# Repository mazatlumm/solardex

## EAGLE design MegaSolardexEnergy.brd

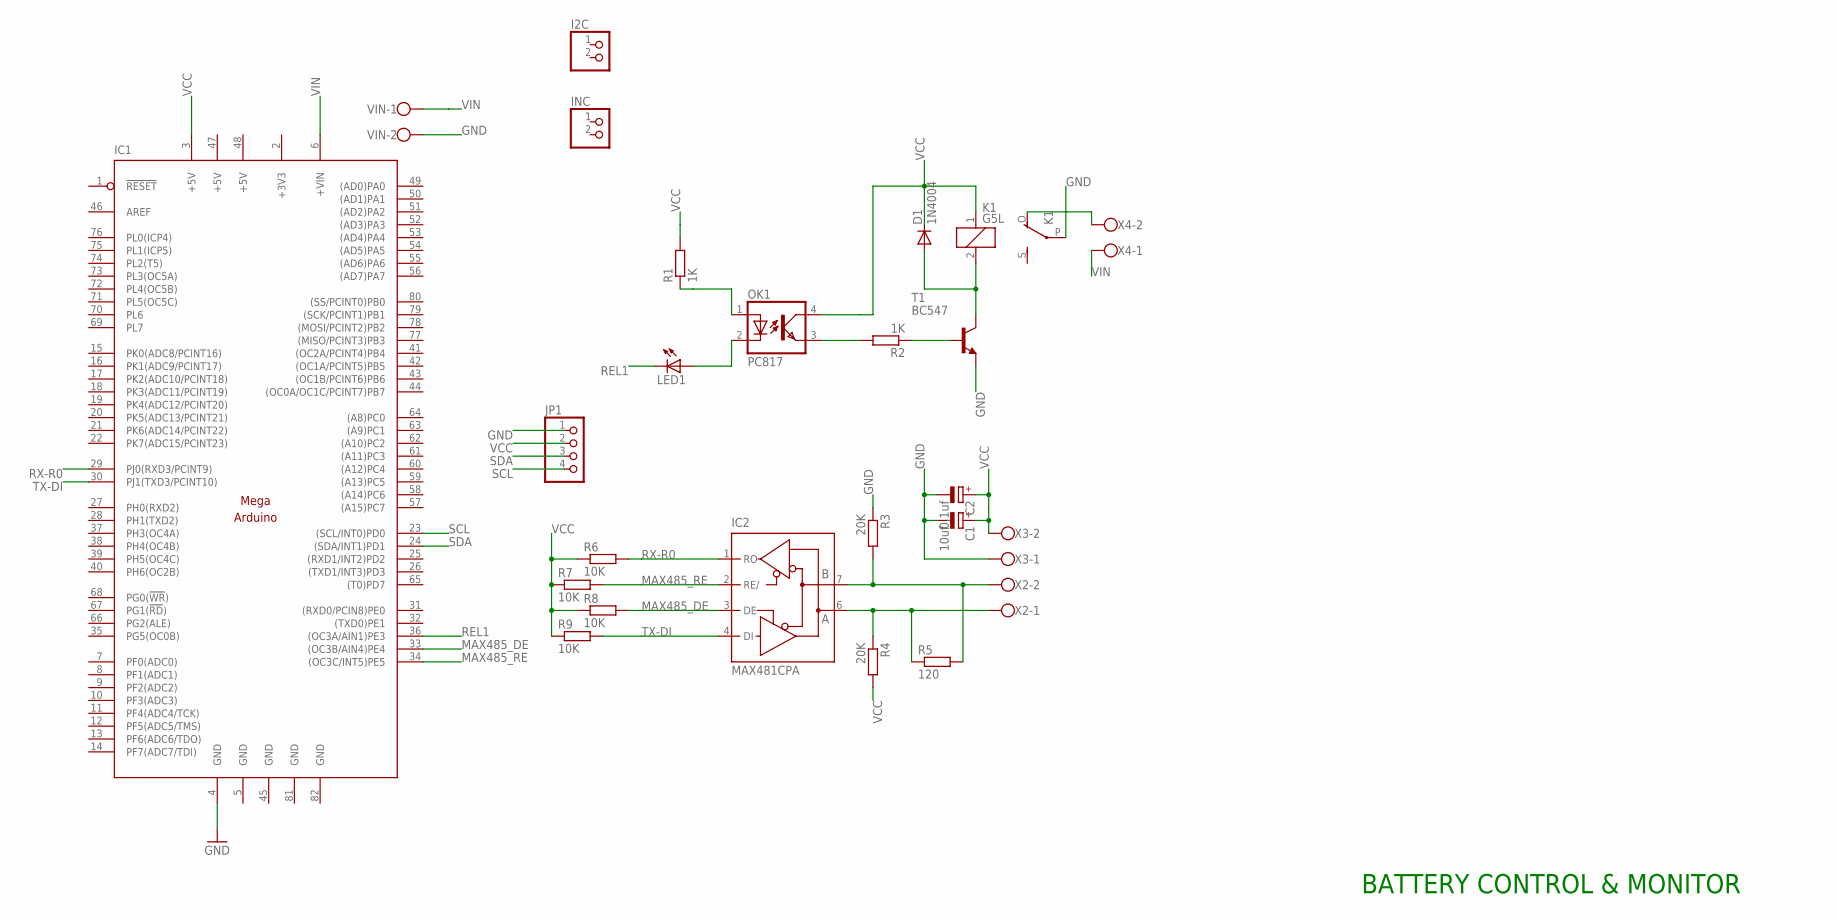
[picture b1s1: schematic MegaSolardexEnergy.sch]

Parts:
C1: 10uf; E2,5-6E
C2: 0,1uf; E2,5-6E
D1: 1N4004; DO41-10
I2C: PINHD-1X2; 1X02
IC1: MEGAARDUINO_1; MEGA_ARDUINO
IC2: MAX481CPA; DIL08
INC: PINHD-1X2; 1X02
JP1: PINHD-1X4; 1X04
K1: G5L; G5LE
LED1: LED5MM
OK1: PC817; DIL04
R1, R2: 1K; 0204/7
R3, R4: 20K; 0204/7
R5: 120; 0204/7
R6, R7, R8, R9: 10K; 0204/7
T1: BC547; TO92
VIN: W237-102
X2, X3, X4: W237-102

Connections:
+3V3: IC1.2 (+3V3)
+5V: IC1.47 (+5V), IC1.48 (+5V)
GND: C1.-, C2.-, IC1.4 (GND), IC1.5 (GND), IC1.45 (GND), IC1.81 (GND), IC1.82 (GND), IC2.5 (GND), JP1.1, K1.P, R3.1, T1.1 (E), VIN.2, X3.1
MAX485_DE: IC1.33 ((OC3B/AIN4)PE4), IC2.3 (DE), R8.2
MAX485_RE: IC1.34 ((OC3C/INT5)PE5), IC2.2 (RE/), R7.2
unnamed: OK1.1 (A), R1.1
unnamed: LED1.A, OK1.2 (C)
unnamed: OK1.3 (EMIT), R2.2
unnamed: R2.1, T1.2 (B)
unnamed: D1.A, K1.2, T1.3 (C)
unnamed: K1.O, X4.2
unnamed: IC2.7 (B), R3.2, R5.2, X2.2
unnamed: IC2.6 (A), R4.1, R5.1, X2.1
REL1: IC1.36 ((OC3A/AIN1)PE3), LED1.K (C)
RX-R0: IC1.29 (PJ0(RXD3/PCINT9)), IC2.1 (RO), R6.2
SCL: IC1.23 ((SCL/INT0)PD0), JP1.4
SDA: IC1.24 ((SDA/INT1)PD1), JP1.3
TX-DI: IC1.30 (PJ1(TXD3/PCINT10)), IC2.4 (DI), R9.2
VCC: C1.+, C2.+, D1.C, IC1.3 (+5V), IC2.8 (VCC), JP1.2, K1.1, OK1.4 (COL), R1.2, R4.2, R6.1, R7.1, R8.1, R9.1, X3.2
VIN: IC1.6 (+VIN), VIN.1, X4.1

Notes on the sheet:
BATTERY CONTROL & MONITOR

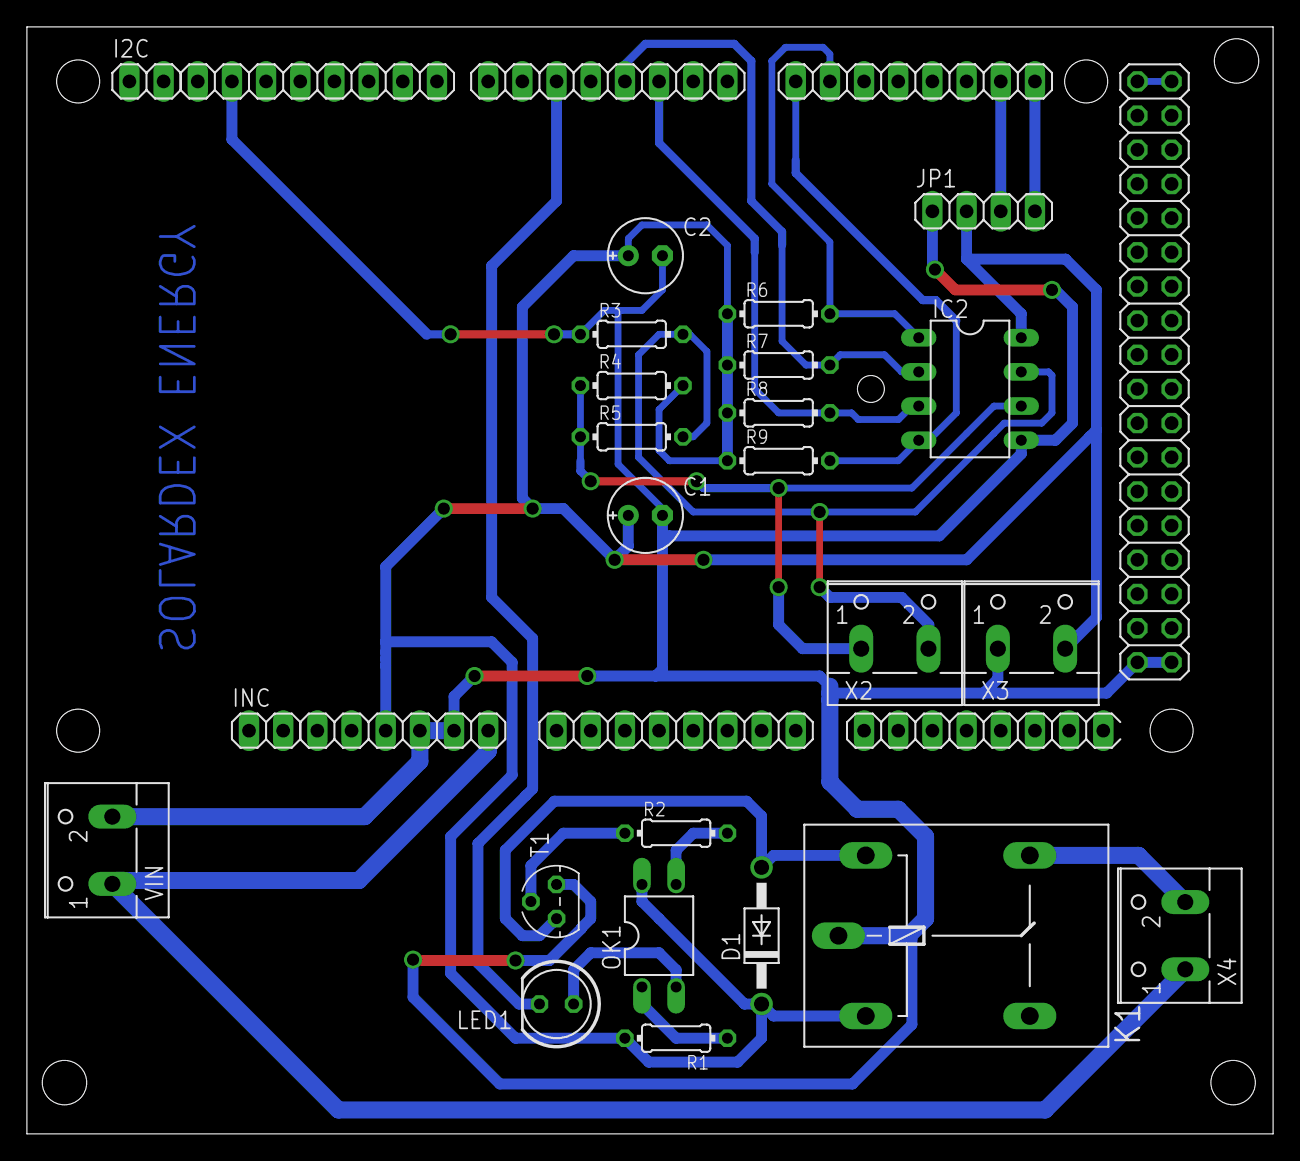
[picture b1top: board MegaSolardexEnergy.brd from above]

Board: 2 copper layers, 92.6 x 82.3 mm, 25 parts (0 on the bottom side), 19 nets.

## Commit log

2023-07-17 web app
